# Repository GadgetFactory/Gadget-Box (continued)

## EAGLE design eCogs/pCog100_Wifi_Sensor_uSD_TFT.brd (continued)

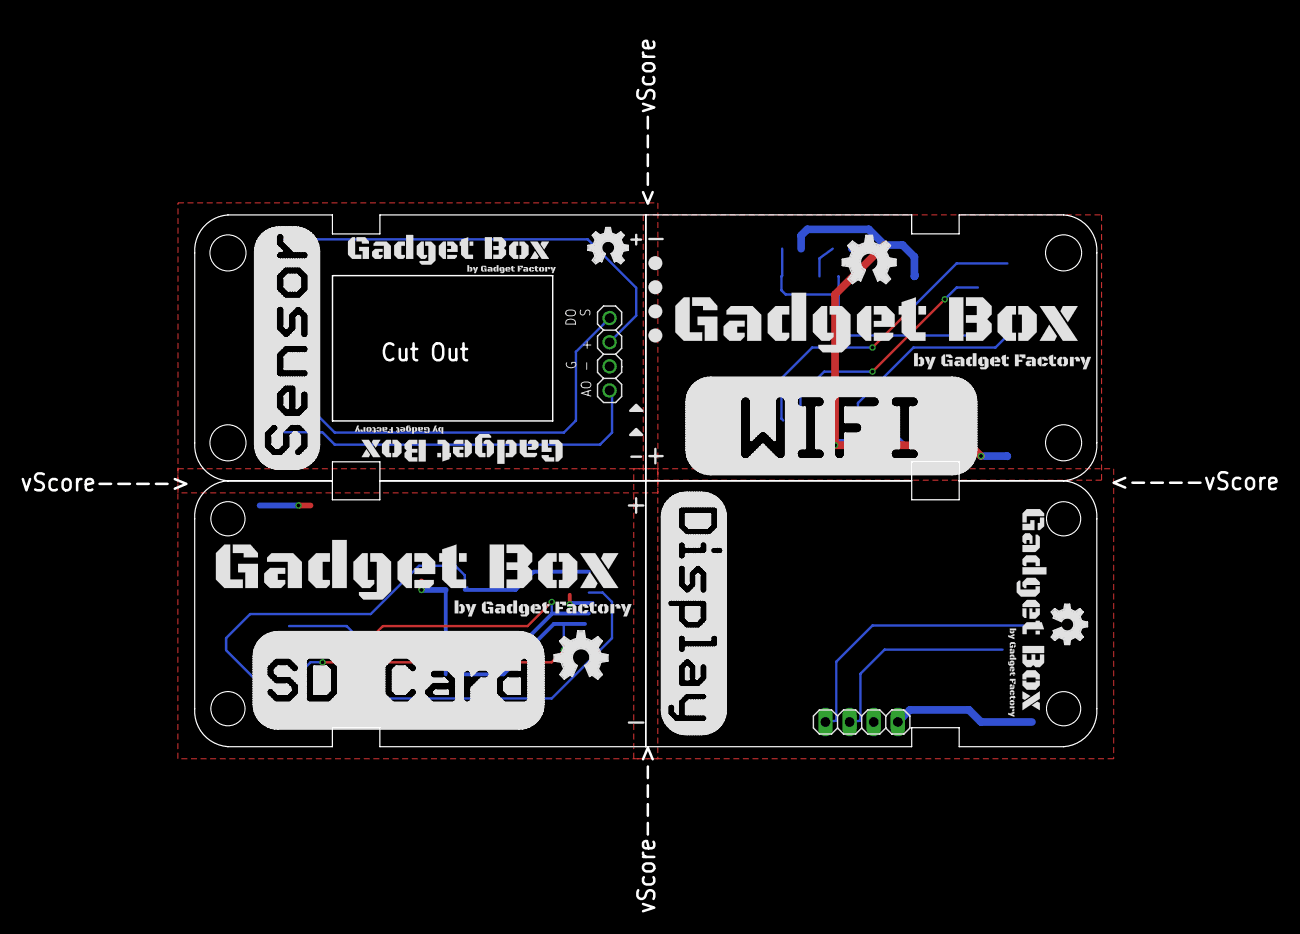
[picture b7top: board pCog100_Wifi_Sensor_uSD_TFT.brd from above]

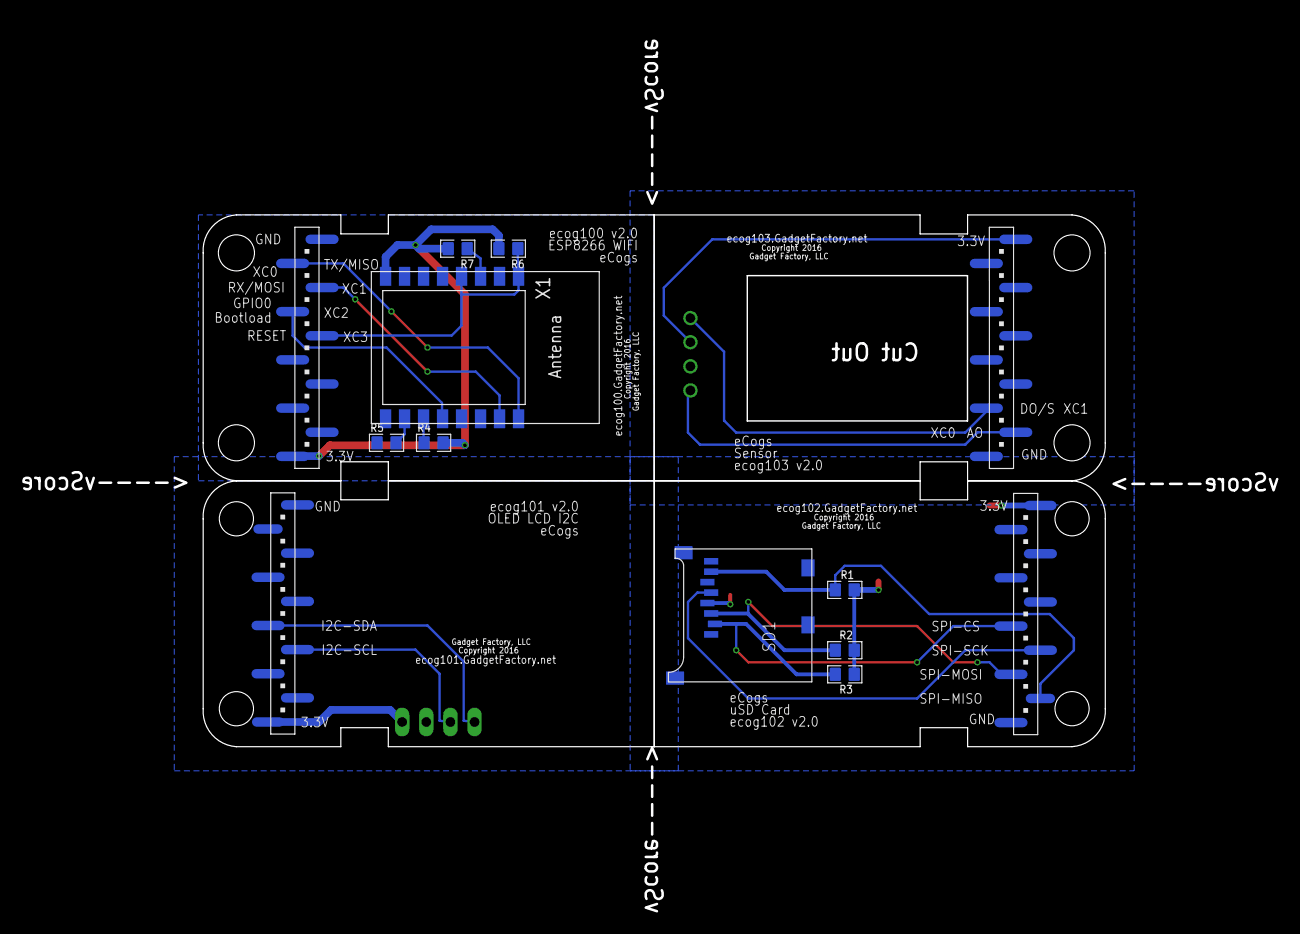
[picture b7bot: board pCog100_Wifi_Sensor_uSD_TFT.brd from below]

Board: 2 copper layers, 95.0 x 56.0 mm, 30 parts (9 on the bottom side), 17 nets.

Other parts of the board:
U$1, U$11: GADGETBOX_TEXT
U$2, U$16: OSHW_FILLX200_NOTEXT
U$3, U$8, U$10: GADGETBOX_SMALL
U$4, U$9: OSHW_FILLX150_NOTEXT
U$6, U$7: LEGEND_ANALOG
U$12, U$13, U$14, U$15: LEGEND_DIO

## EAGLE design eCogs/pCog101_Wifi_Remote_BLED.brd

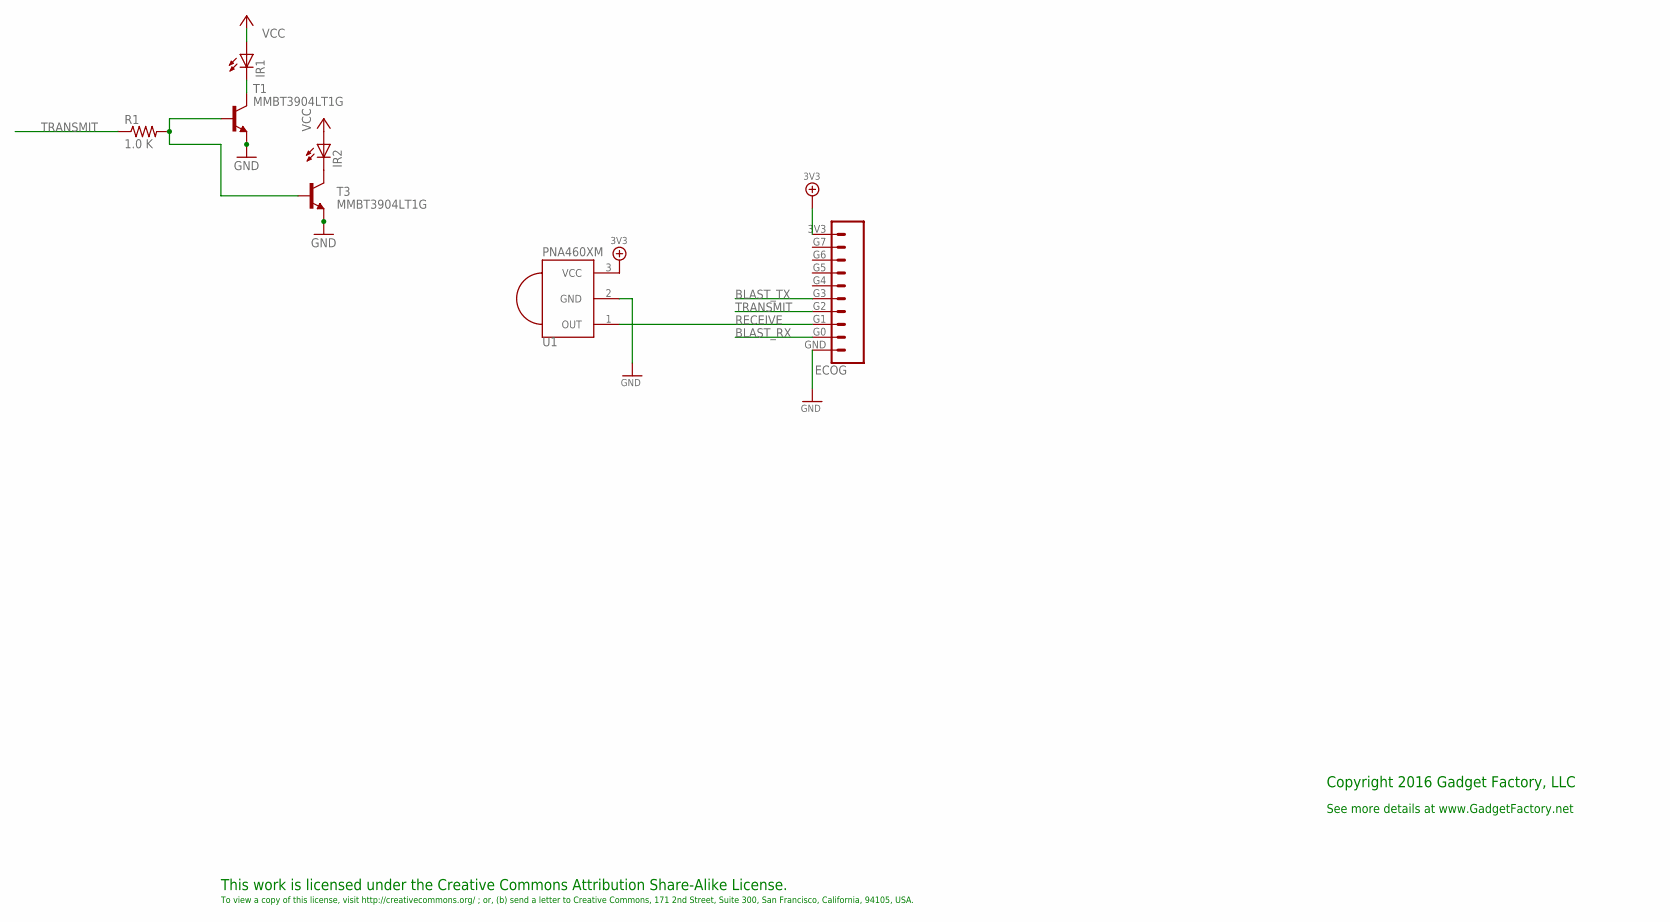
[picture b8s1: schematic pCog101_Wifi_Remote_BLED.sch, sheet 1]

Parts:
ECOG: ECOG_GENERAL_ROWECOG_GENERAL_SMD; ECOG_GENERAL_SMD; PARTNO NREC010SABC-M30RC,SULLINS CONNECTOR SOL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
IR1: LED5MM; PARTNO IR333C/H0/L10,everlight,dk,1080-1082-ND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; DIGIKEY 1080-1082-ND
IR2: LED5MM; PARTNO IR333C/H0/L10,everlight,dk,1080-1082-ND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; DIGIKEY 1080-1080-ND
R1: 1.0 K; R0805; PARTNO RC0805JR-071KL,YAGEO (VA),dk,311-1.0KAR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; DIGIKEY 311-1.0KARCT-ND
T1, T3: MMBT3904LT1G; SOT23-BEC; PARTNO MMBT3904LT1G,on semiconductor,dk,MMBT39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; DIGIKEY MMBT3904LT1GOSCT-ND
U1: PNA460XM; PARTNO TSOP38238,VISHAY DALE (VA),dk,751-1227-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; DIGIKEY 751-1227-ND

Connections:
3V3: ECOG.3V3, IR1.A, IR2.A, U1.3 (VCC); also elsewhere on the board
BLAST_RX: ECOG.G0
BLAST_TX: ECOG.G3
GND: ECOG.GND, T1.E, T3.E, U1.2 (GND); also elsewhere on the board
unnamed: IR1.K (C), T1.C
unnamed: IR2.K (C), T3.C
unnamed: R1.2, T1.B, T3.B
RECEIVE: ECOG.G1, U1.1 (OUT)
TRANSMIT: ECOG.G2, R1.1

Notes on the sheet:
This work is licensed under the Creative Commons Attribution Share-Alike License.
To view a copy of this license, visit http://creativecommons.org/ ; or, (b) send a letter to Creative Commons, 171 2nd Street, Suite 300, San Francisco, California, 94105, USA.
Copyright 2016 Gadget Factory, LLC
See more details at www.GadgetFactory.net

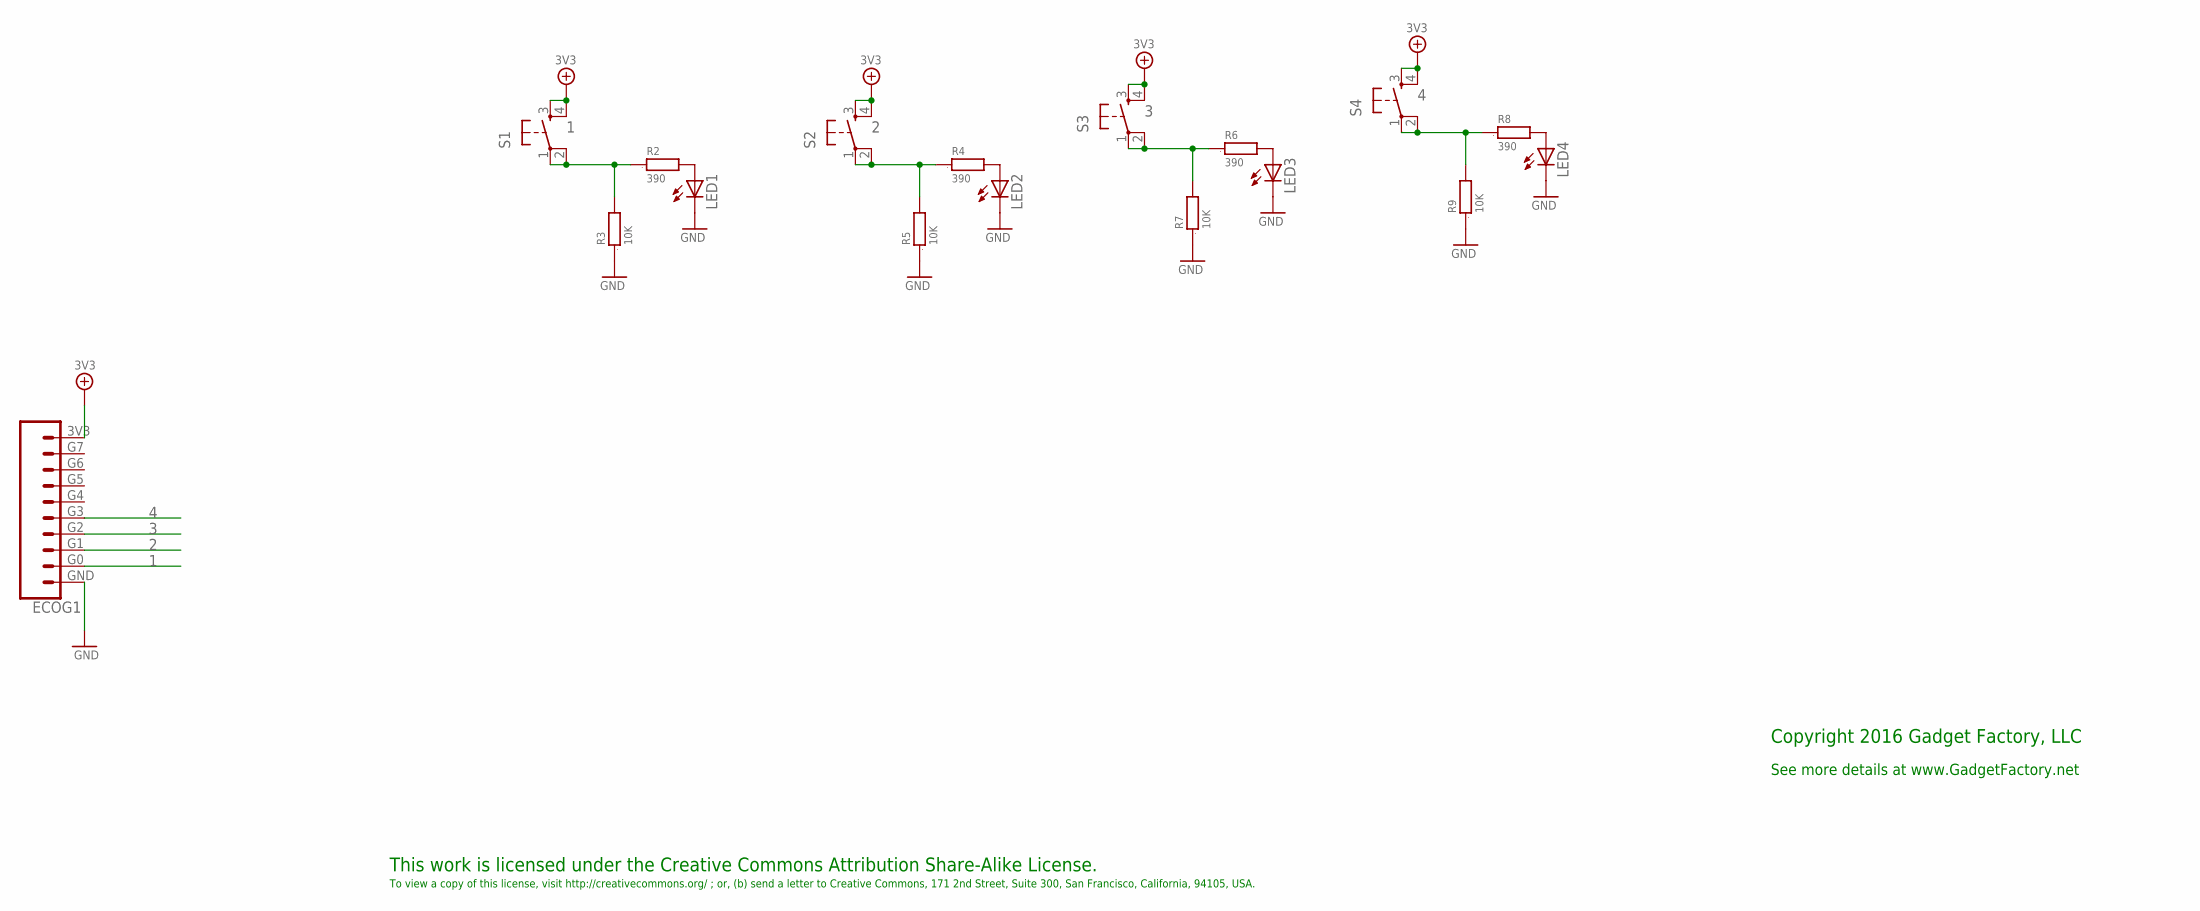
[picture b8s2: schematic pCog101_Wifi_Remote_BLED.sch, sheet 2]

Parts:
ECOG1: ECOG_GENERAL_ROWECOG_GENERAL_SMD; ECOG_GENERAL_SMD; PARTNO NREC010SABC-M30RC,SULLINS CONNECTOR SOL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
LED1, LED2, LED3, LED4: LEDCHIP-LED0805; CHIP-LED0805; PARTNO LTST-C170KGKT,LITE-ON INC (VA),DK,160-1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; DIGIKEY 475-1410-2-ND
R2, R4, R6, R8: 390; 0805; PARTNO MCR10EZPJ391,ROHM SEMICONDUCTOR (PASSIV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; DIGIKEY RMCF0805JT390RCT-ND
R3, R5, R7, R9: 10K; 0805; PARTNO RC0805JR-0710KL,YAGEO (VA),dk,311-10KAR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; DIGIKEY RMCF0805JT10K0CT-ND
S1, S2, S3, S4: TAC_SWITCHPTH; TACTILE-PTH; PARTNO MJTP1230,Apem,dk,679-2428-ND,Tactile Sw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; DIGIKEY 679-2428-ND

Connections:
1: ECOG1.G0, R2.1, R3.2, S1.1, S1.2
2: ECOG1.G1, R4.1, R5.2, S2.1, S2.2
3: ECOG1.G2, R6.1, R7.2, S3.1, S3.2
3V3: ECOG1.3V3, S1.3, S1.4, S2.3, S2.4, S3.3, S3.4, S4.3, S4.4; also elsewhere on the board
4: ECOG1.G3, R8.1, R9.2, S4.1, S4.2
GND: ECOG1.GND, LED1.C, LED2.C, LED3.C, LED4.C, R3.1, R5.1, R7.1, R9.1; also elsewhere on the board
unnamed: LED1.A, R2.2
unnamed: LED2.A, R4.2
unnamed: LED3.A, R6.2
unnamed: LED4.A, R8.2

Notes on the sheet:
This work is licensed under the Creative Commons Attribution Share-Alike License.
To view a copy of this license, visit http://creativecommons.org/ ; or, (b) send a letter to Creative Commons, 171 2nd Street, Suite 300, San Francisco, California, 94105, USA.
Copyright 2016 Gadget Factory, LLC
See more details at www.GadgetFactory.net

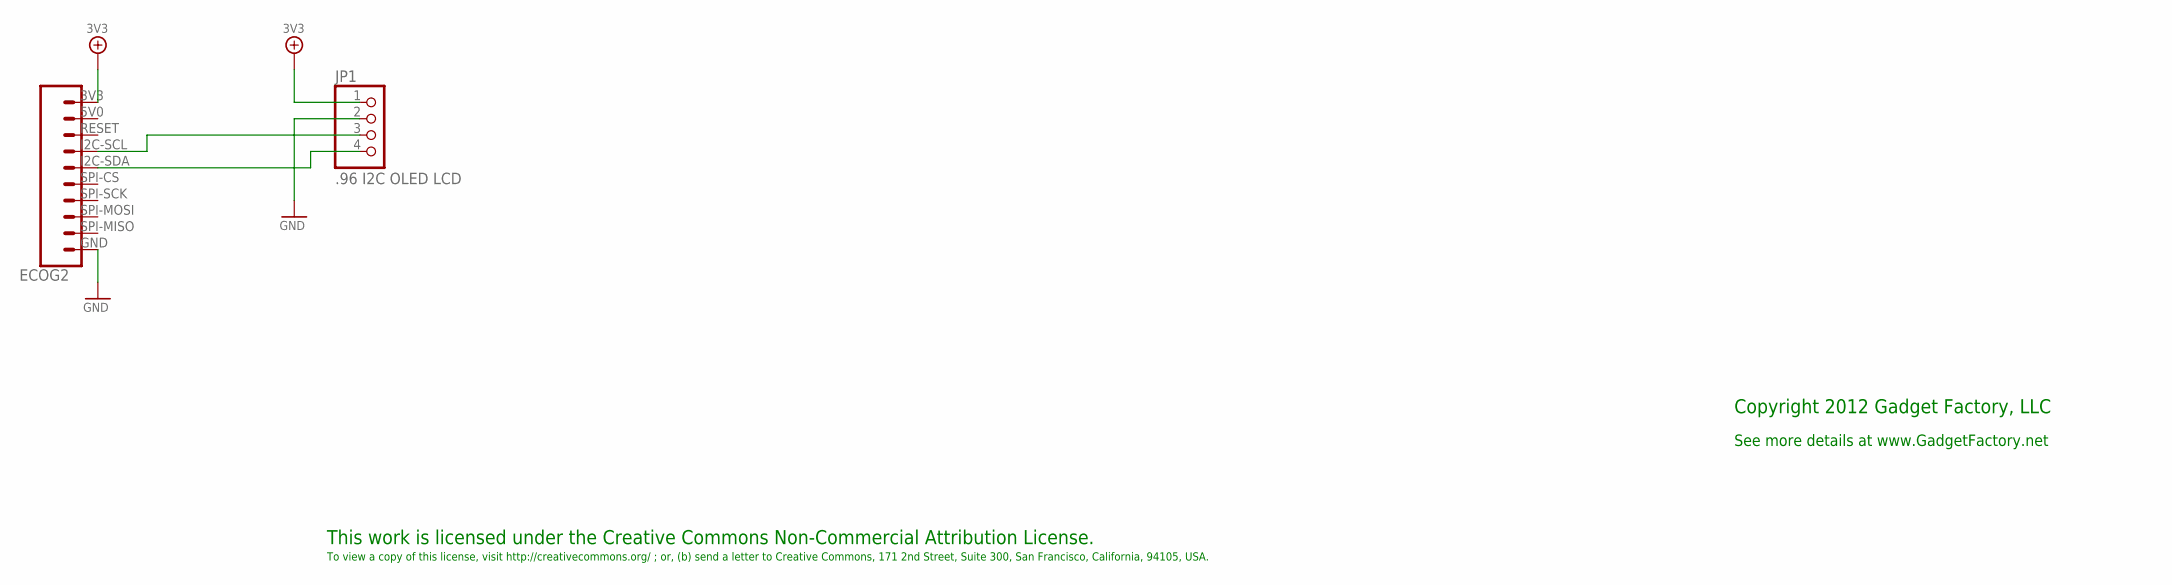
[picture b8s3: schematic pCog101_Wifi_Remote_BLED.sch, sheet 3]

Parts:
ECOG2: ECOG_BUSES_ROWECOG_BUSES_SMD; ECOG_BUSES_SMD; PARTNO NREC010SABC-M30RC,SULLINS CONNECTOR SOL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
JP1: .96 I2C OLED LCD; 1X04; PARTNO 346540,unknown,dx.com,346540,"0.96"" 12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

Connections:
3V3: ECOG2.3V3, JP1.1; also elsewhere on the board
GND: ECOG2.GND, JP1.2; also elsewhere on the board
unnamed: ECOG2.I2C-SDA, JP1.4
unnamed: ECOG2.I2C-SCL, JP1.3

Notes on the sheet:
This work is licensed under the Creative Commons Non-Commercial Attribution License.
To view a copy of this license, visit http://creativecommons.org/ ; or, (b) send a letter to Creative Commons, 171 2nd Street, Suite 300, San Francisco, California, 94105, USA.
Copyright 2012 Gadget Factory, LLC
See more details at www.GadgetFactory.net

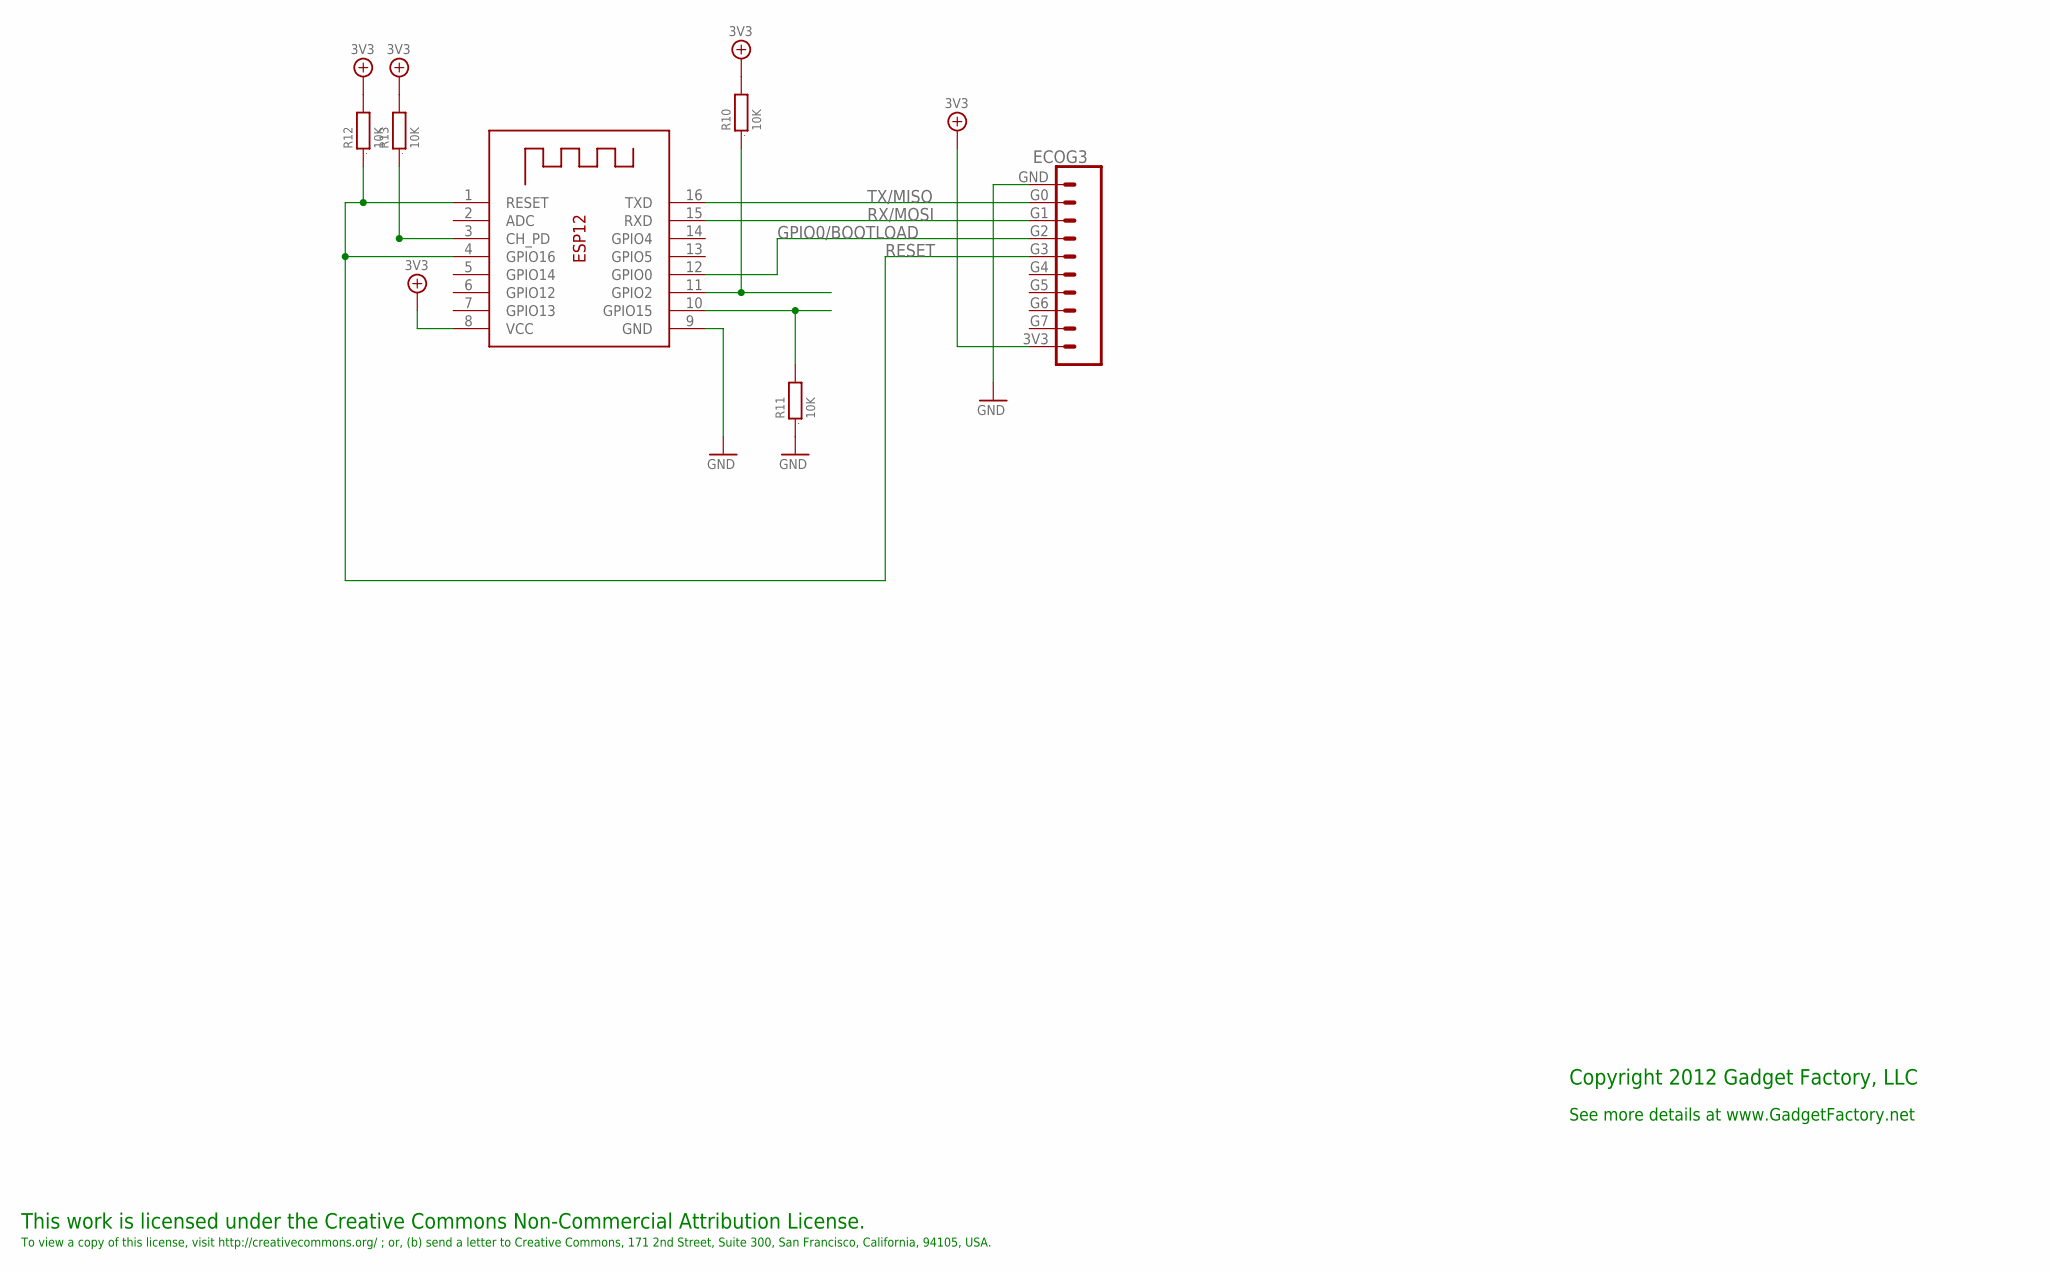
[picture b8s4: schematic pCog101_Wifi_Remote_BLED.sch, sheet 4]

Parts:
ECOG3: ECOG_GENERAL_ROWECOG_GENERAL_SMD; ECOG_GENERAL_SMD; PARTNO NREC010SABC-M30RC,SULLINS CONNECTOR SOL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
R10, R11, R12, R13: 10K; 0805; PARTNO RC0805JR-0710KL,YAGEO (VA),dk,311-10KAR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; DIGIKEY RMCF0805JT10K0CT-ND
X1: ESP-12; PARTNO 385646,AI-Thinker,dx.com,385646,ESP8266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

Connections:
3V3: ECOG3.3V3, R10.2, R12.2, R13.2, X1.8 (VCC); also elsewhere on the board
GND: ECOG3.GND, R11.1, X1.9 (GND); also elsewhere on the board
GPIO0/BOOTLOAD: ECOG3.G2, X1.12 (GPIO0)
unnamed: R10.1, X1.11 (GPIO2)
unnamed: R11.2, X1.10 (GPIO15)
unnamed: R13.1, X1.3 (CH_PD)
RESET: ECOG3.G3, R12.1, X1.1 (RESET), X1.4 (GPIO16)
RX/MOSI: ECOG3.G1, X1.15 (RXD)
TX/MISO: ECOG3.G0, X1.16 (TXD)

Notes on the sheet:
This work is licensed under the Creative Commons Non-Commercial Attribution License.
To view a copy of this license, visit http://creativecommons.org/ ; or, (b) send a letter to Creative Commons, 171 2nd Street, Suite 300, San Francisco, California, 94105, USA.
Copyright 2012 Gadget Factory, LLC
See more details at www.GadgetFactory.net

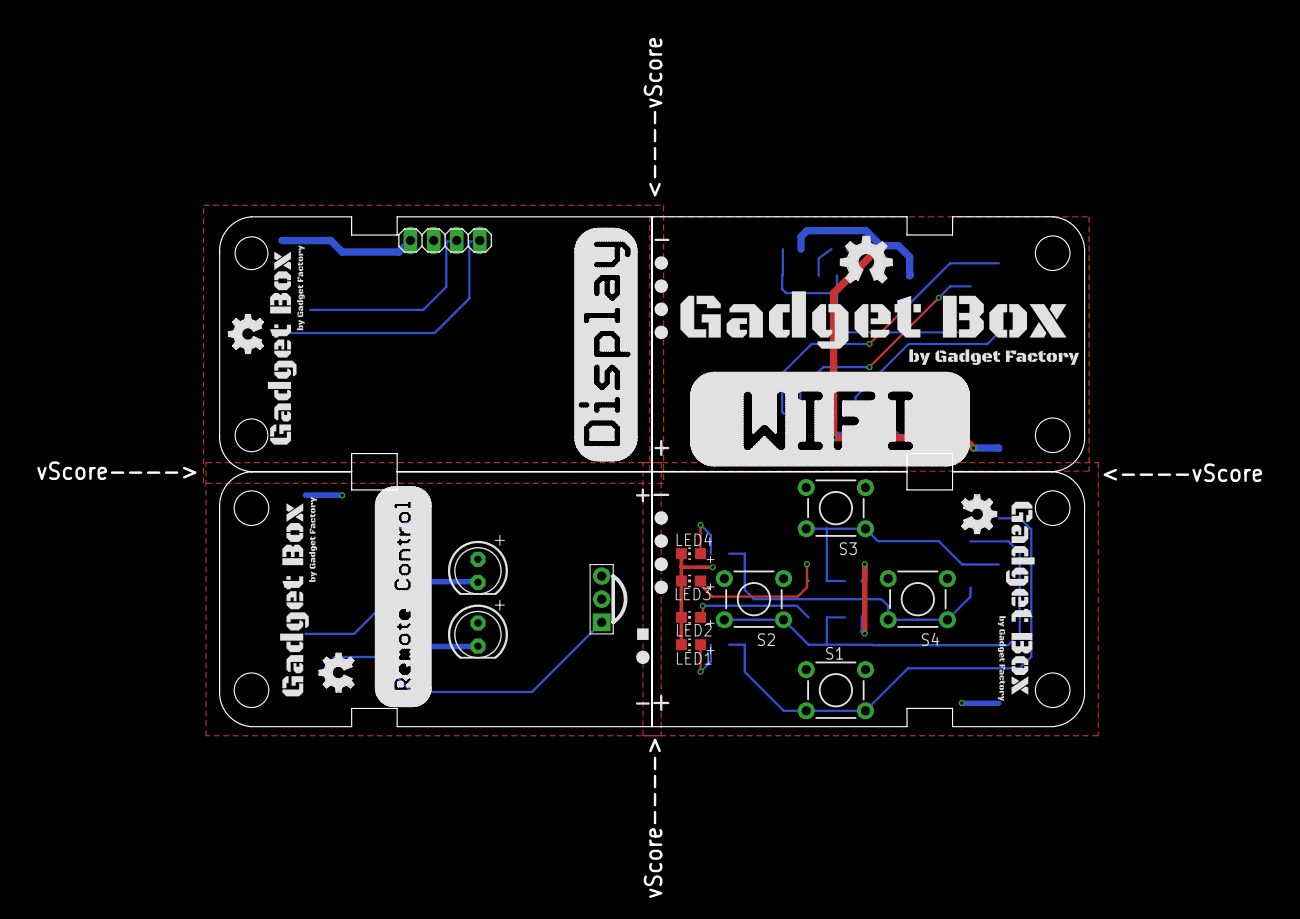
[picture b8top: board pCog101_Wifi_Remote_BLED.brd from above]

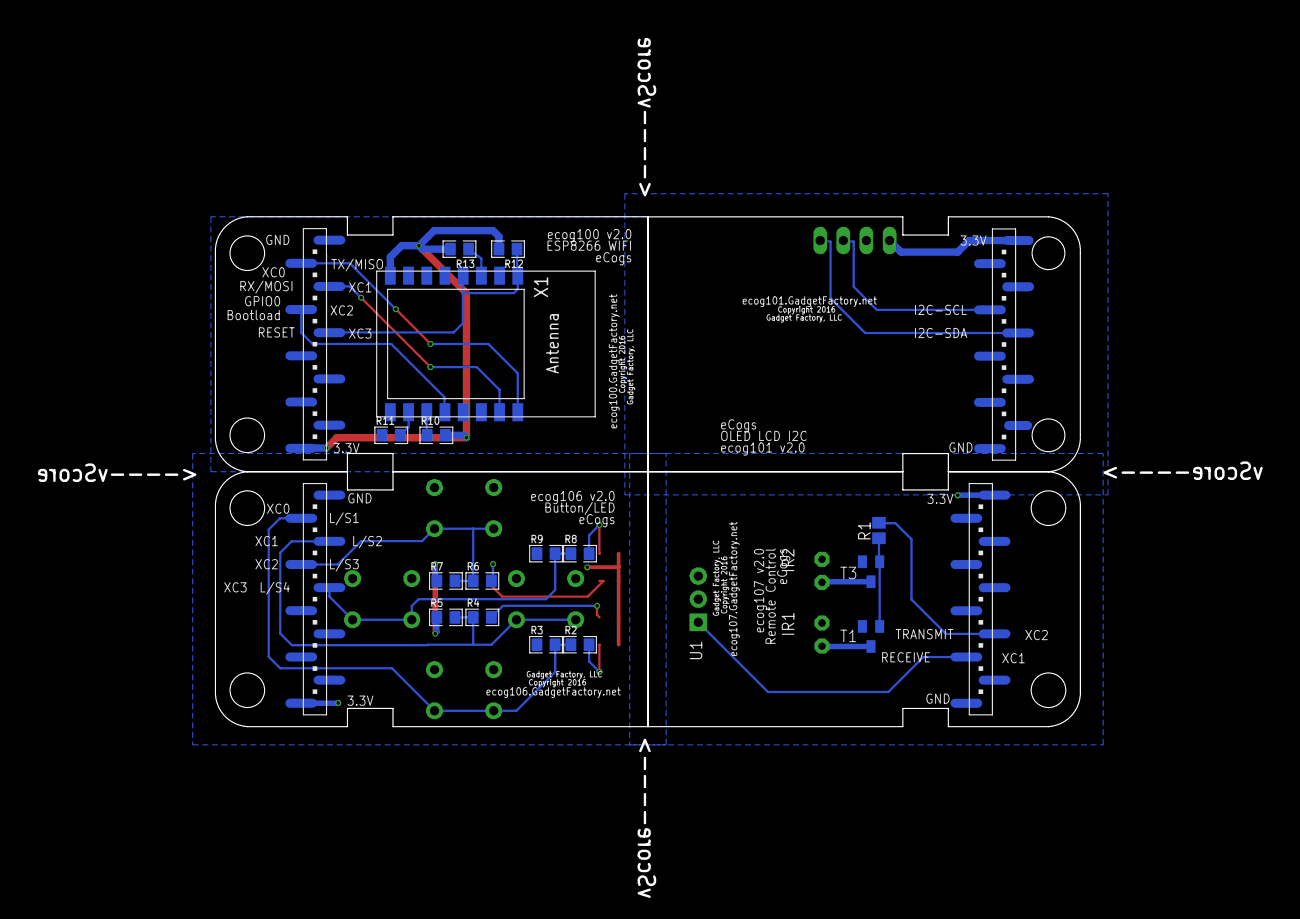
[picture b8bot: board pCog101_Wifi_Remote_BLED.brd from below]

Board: 2 copper layers, 95.0 x 56.0 mm, 50 parts (16 on the bottom side), 24 nets.

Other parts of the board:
U$1, U$3, U$4, U$7, U$8, U$14, U$15, U$16, U$17: LEGEND_DIO
U$2: LEGEND_PWM
U$5, U$9, U$11: GADGETBOX_SMALL
U$6, U$10, U$12: OSHW_FILLX150_NOTEXT
U$13: GADGETBOX_TEXT
U$18: OSHW_FILLX200_NOTEXT
